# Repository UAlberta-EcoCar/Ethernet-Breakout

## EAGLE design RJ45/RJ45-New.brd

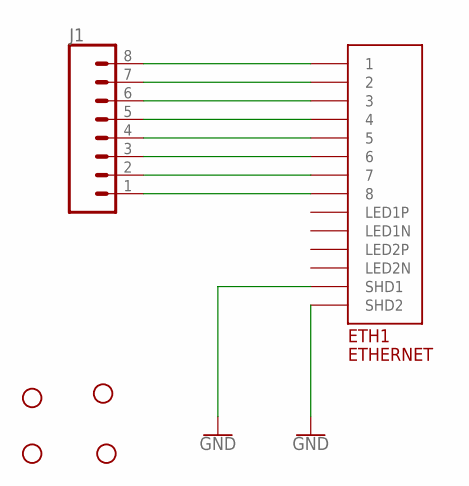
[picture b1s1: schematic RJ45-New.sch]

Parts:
ETH1: ETHERNET; A122645-ND
H1, H2, H3, H4: STAND-OFF
J1: CONN_08"; 1X08

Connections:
GND: ETH1.P$13 (SHD1), ETH1.P$14 (SHD2)
unnamed: ETH1.P$1 (1), J1.8
unnamed: ETH1.P$2 (2), J1.7
unnamed: ETH1.P$3 (3), J1.6
unnamed: ETH1.P$4 (4), J1.5
unnamed: ETH1.P$5 (5), J1.4
unnamed: ETH1.P$7 (7), J1.2
unnamed: ETH1.P$6 (6), J1.3
unnamed: ETH1.P$8 (8), J1.1

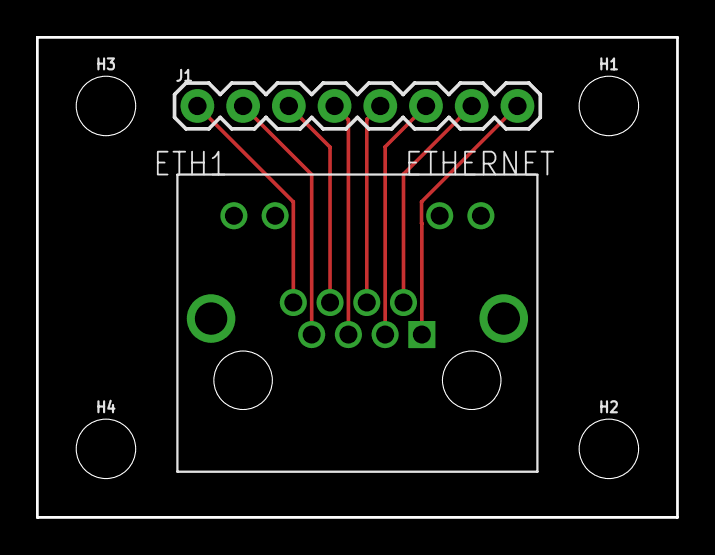
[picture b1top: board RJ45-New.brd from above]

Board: 2 copper layers, 35.6 x 26.7 mm, 6 parts (0 on the bottom side), 9 nets.

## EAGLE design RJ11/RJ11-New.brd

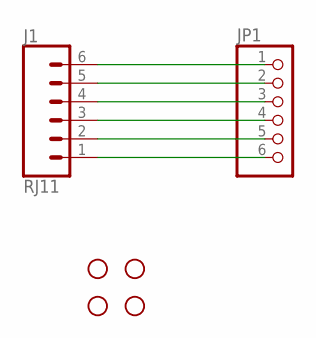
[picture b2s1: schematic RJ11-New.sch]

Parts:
H1, H2, H3, H4: STAND-OFF
J1: RJ11; RJ11-6
JP1: PINHD-1X6; 1X06

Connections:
unnamed: J1.6, JP1.1
unnamed: J1.5, JP1.2
unnamed: J1.4, JP1.3
unnamed: J1.3, JP1.4
unnamed: J1.2, JP1.5
unnamed: J1.1, JP1.6

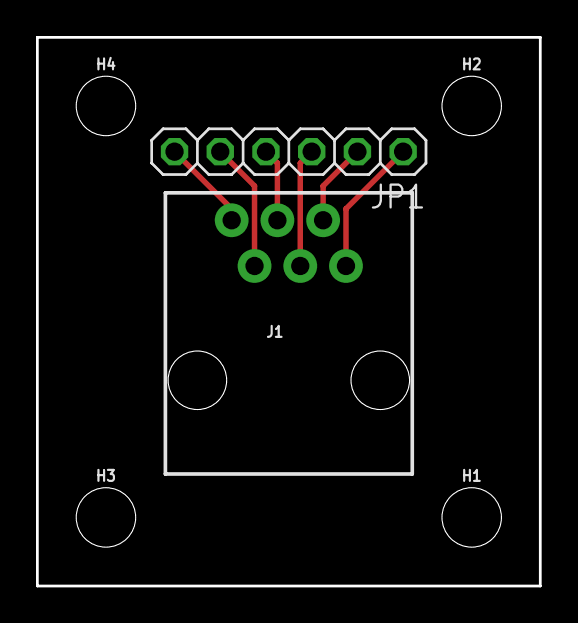
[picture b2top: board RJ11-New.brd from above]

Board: 2 copper layers, 27.9 x 30.5 mm, 6 parts (0 on the bottom side), 6 nets.

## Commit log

2017-10-03 added the new RJ11 and RJ45 breakout boards
    both boards ready for print unless we need to flip the RJ11 part still
2017-10-10 Gerbers Generated

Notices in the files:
parts and their libraries:
SparkFun-Hardware: Licensing: Creative Commons ShareAlike 4.0 International - https://creativecommons.org/licenses/by-sa/4.0
